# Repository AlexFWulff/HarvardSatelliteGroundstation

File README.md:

# Harvard Satellite Groundstation Code
This repository contains all the software for the groundstation, including OpenLST for the transmitter and Groundstation GNU Radio software.

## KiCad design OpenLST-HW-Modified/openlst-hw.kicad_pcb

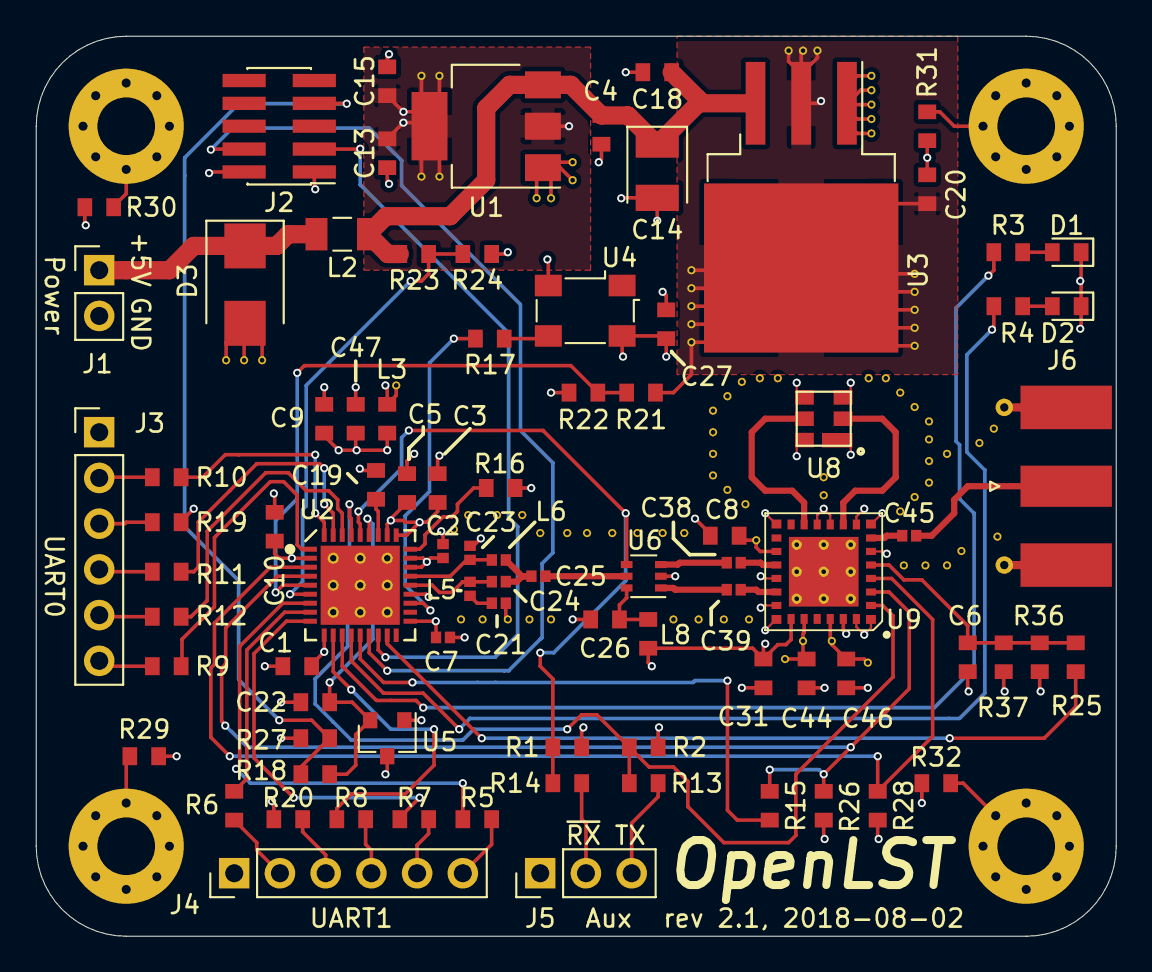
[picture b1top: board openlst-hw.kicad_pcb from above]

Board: 4 copper layers, 60.0 x 50.0 mm, 90 parts (0 on the bottom side), 65 nets.

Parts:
C1, C3, C5, C6, C8, C10, C15, C26, C27, C31: 0.1u; C_0603_1608Metric
C2, C7, C21, C25, C38, C39, C45: 220p; C_0402_1005Metric
C4, C13, C18, C20: 10u; C_0603_1608Metric
C9, C44, C46, C47: 1u; C_0603_1608Metric
C14: 100u; CP_EIA-3528-15_AVX-H
C19, C22: 1n; C_0603_1608Metric
C23, C24: 3.9p; C_0402_1005Metric
D1, D2: LED; LED_0603_1608Metric
D3: STPS340U; D_SMB
J1: 5VDC; PinHeader_1x02_P2.54mm_Vertical
J2: CC Prog/Debug; PinHeader_2x05_P1.27mm_Vertical_SMD
J3: UART0; PinHeader_1x06_P2.54mm_Vertical
J4: UART1; PinHeader_1x06_P2.54mm_Vertical
J5: Control Outputs; PinHeader_1x03_P2.54mm_Vertical
J6: ANT; SMA_Molex_73251-1153_EdgeMount_Horizontal
L2: Z=500 @ 100M; L_1206_3216Metric
L3, L8: Z=1k @ 100M; L_0603_1608Metric
L5, L6: 27n; L_0402_1005Metric
MK1, MK2, MK3, MK4: M3_Hole; MountingHole_3.2mm_M3_Pad_Via
R1, R2, R3, R4, R18, R26, R28: 1K; R_0603_1608Metric
R5, R6, R7, R8, R9, R10, R11, R12, R13, R14, R17: 100; R_0603_1608Metric
R15, R19, R20, R25, R29, R30, R31, R32: DNI; R_0603_1608Metric
R16: 56K; R_0603_1608Metric
R21, R23, R27: 33K; R_0603_1608Metric
R22, R24: 10K; R_0603_1608Metric
R36: 5K6; R_0603_1608Metric
R37: 3K3; R_0603_1608Metric
U1: LM1117-3.3; SOT-223-3_TabPin2
U2: CC1110; TI_CC_QFN36
U3: LT1086-3.6; TO-263-3_TabPin2
U4: FOX924 27MHz; Oscillator_SMD_Fordahl_DFAS15-4Pin_5.0x3.2mm
U5: TLV803S; SOT-23
U6: PE4259; SOT-363_SC-70-6
U8: STA1120A; SF2136E
U9: RFFM6403; Qorvo_LGA_28_ThermalVias

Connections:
+3V3: C13.1, C15.1, C27.1, C31.1, J2.2, L3.1, L8.1, R1.1, R19.1, R20.1, R26.1, R27.2, U1.2, U4.4, U5.3, U9.23
+5V: C4.1, C14.1, C18.1, L2.1, R23.2, U1.3, U3.3
/3V3_FILT: C1.1, C2.1, C3.1, C5.1, C7.1, C9.2, C10.1, C47.2, L3.2, U2.2, U2.10, U2.19, U2.22, U2.25, U2.26, U2.28, U2.29
/AN0: R21.1, R22.2, U2.5
/AN1: R23.1, R24.2, U2.6
/LST_TX_MODE: R2.2, R13.1, U2.33, U9.2
/PA_VAPC: C6.1, R25.1, R36.1, R37.2, U9.5
/PROG_DC: J2.3, U2.16
/PROG_DD: J2.4, U2.15
/RF_BYP: R28.1, U2.3, U9.4
/RF_EN: R15.1, R26.2, U2.4, U9.3
/UART0_CTS: J3.6, R9.2
/UART0_RTS: J3.2, R10.2
/UART0_RX: J3.4, R11.2
/UART0_TX: J3.5, R12.2
/UART1_CTS: J4.6, R5.2
/UART1_RTS: J4.2, R6.2
/UART1_RX: J4.4, R8.2
/UART1_TX: J4.5, R7.2
/~LST_RESET: J2.7, R18.2, R27.1
/~LST_RX_MODE: R1.2, R14.1, U2.32, U6.4
GND: C1.2, C2.2, C3.2, C4.2, C5.2, C6.2, C7.2, C8.2, C9.1, C10.2, C13.2, C14.2, C15.2, C18.2, C19.2, C20.2, C21.1, C22.2, C23.1, C26.2, C27.2, C31.2, C44.2, C46.2, C47.1, D1.1, D2.1, D3.2, J1.2, J2.1, J3.1, J4.1, J5.1, J6.2, R2.1, R16.1, R22.1, R24.1, R28.2, R29.1, R30.1, R31.1, R32.1, R36.2, U1.1, U2.37, U3.1, U4.2, U5.1, U6.2, U8.1, U8.3, U8.4, U8.5, U9.1, U9.6, U9.8, U9.9, U9.11, U9.12, U9.15, U9.19, U9.21, U9.22, U9.27, U9.28, U9.29
unnamed: C19.1, U2.30
unnamed: C21.2, L5.1
unnamed: C22.1, R18.1, U2.31, U5.2
unnamed: C23.2, L6.1, U2.24
unnamed: C24.1, L5.2, U2.23
unnamed: C24.2, C25.1, L6.2
unnamed: C25.2, U6.5
unnamed: C26.1, L8.2, U6.6
unnamed: C38.1, U6.3
unnamed: C38.2, U9.18
unnamed: C39.1, U6.1
unnamed: C39.2, U9.20
unnamed: C45.1, J6.1
unnamed: C45.2, U9.7
unnamed: D1.2, R3.1
unnamed: D2.2, R4.1
unnamed: D3.1, J1.1, L2.2
unnamed: J3.3, R19.2
unnamed: J4.3, R20.2
unnamed: J5.2, R14.2
unnamed: J5.3, R13.2
unnamed: MK1.1, R29.2
unnamed: MK2.1, R30.2
unnamed: MK3.1, R31.2
unnamed: MK4.1, R32.2
unnamed: R3.2, U2.12
unnamed: R4.2, U2.13
unnamed: R5.1, U2.7
unnamed: R6.1, U2.8
unnamed: R7.1, U2.9
unnamed: R8.1, U2.11
unnamed: R9.1, U2.1
unnamed: R10.1, U2.36
unnamed: R11.1, U2.35
unnamed: R12.1, U2.34
unnamed: R15.2, U2.14
unnamed: R16.2, U2.27
unnamed: R17.1, U4.3
unnamed: R17.2, U2.21
unnamed: R25.2, U2.17
unnamed: U8.2, U9.10
unnamed: U8.6, U9.13
VCC_3V6: C8.1, C20.1, C44.1, C46.1, R21.2, R37.1, U3.2, U9.17, U9.24, U9.26

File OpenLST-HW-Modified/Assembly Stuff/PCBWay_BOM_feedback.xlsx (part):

Reference | Value | Footprint | Datasheet | Manuf | ManufPN | Supplier | SupplierPN | Unit price | 5sets | PCBWay feedback | Customer Comments
L6 | 27n | Inductor_SMD:L_0402_1005Metric | http://search.murata.co.jp/Ceramy/image/img/P02/JELF243A-0050.pdf | Murata | LQW15AN27NJ00D | Digikey | 490-1151-1-ND | 0.105 | 0.52500000000000002
J6 | ANT | Connector_Coaxial:SMA_Molex_73251-1153_EdgeMount_Horizontal | https://www.molex.com/pdm_docs/sd/732511150_sd.pdf | Molex | 732511150 | Digikey | WM5534-ND | 4.83 | 24.15 | 5-7work days
C45 | 220p | Capacitor_SMD:C_0402_1005Metric | https://api.kemet.com/component-edge/download/datasheet/C040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 | Kemet | C0402C221J2GACAUTO | Digikey | 399-11552-1-ND | 0.315 | 1.575 | 5-7work days
C25 | 220p | Capacitor_SMD:C_0402_1005Metric | https://api.kemet.com/component-edge/download/datasheet/C040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 | Kemet | C0402C221J2GACAUTO | Digikey | 399-11552-1-ND | 0.315 | 1.575 | 5-7work days
C24 | 3.9p | Capacitor_SMD:C_0402_1005Metric | http://search.murata.co.jp/Ceramy/image/img/A01X/G101/ENG/GJ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 | Murata | GJM1555C1H3R9CB01D | Digikey | 490-3097-1-ND | 0.21 | 1.05 | 4300pcs
L5 | 27n | Inductor_SMD:L_0402_1005Metric | http://search.murata.co.jp/Ceramy/image/img/P02/JELF243A-0050.pdf | Murata | LQW15AN27NJ00D | Digikey | 490-1151-1-ND | 0.105 | 0.52500000000000002
C21 | 220p | Capacitor_SMD:C_0402_1005Metric | https://api.kemet.com/component-edge/download/datasheet/C040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 | Kemet | C0402C221J2GACAUTO | Digikey | 399-11552-1-ND | 0.315 | 1.575 | 5-7work days
U1 | LM1117-3.3 | Package_TO_SOT_SMD:SOT-223-3_TabPin2 | http://www.ti.com/lit/ds/symlink/lm1117.pdf | Texas Instruments | LM1117IMP-3.3/NOPB | Digikey | LM1117IMP-3.3/NOPBCT-ND | 0.73499999999999999 | 3.6749999999999998
C4 | 10u | Capacitor_SMD:C_0603_1608Metric | http://search.murata.co.jp/Ceramy/image/img/A01X/G101/ENG/GR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 | Murata | GRT188C81A106ME13D | Digikey | 490-12283-1-ND | 0.21 | 1.05
C13 | 10u | Capacitor_SMD:C_0603_1608Metric | http://search.murata.co.jp/Ceramy/image/img/A01X/G101/ENG/GR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 | Murata | GRT188C81A106ME13D | Digikey | 490-12283-1-ND | 0.21 | 1.05
C15 | 0.1u | Capacitor_SMD:C_0603_1608Metric | http://datasheets.avx.com/AutoMLCC.pdf | AVX | 0603YC104K4T4A | Digikey | 478-9382-1-ND | 0.105 | 0.52500000000000002
J1 | 5VDC | Connector_PinHeader_2.54mm:PinHeader_1x02_P2.54mm_Vertical |  |  |  |  |  | 0.105 | 0.52500000000000002 | 1*2pin header 2.54mm
D3 | STPS340U | Diode_SMD:D_SMB | http://www.st.com/content/ccc/resource/technical/document/da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 | STMicroelectronics | STPS340U | Digikey | 497-2465-1-ND | 0.315 | 1.575
L2 | Z=500 @ 100M | Inductor_SMD:L_1206_3216Metric | https://assets.lairdtech.com/home/brandworld/files/MI1206L50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 | Laird | MI1206L501R-10 | Digikey | 240-2407-1-ND | 0.63 | 3.15 | 5-7work days
C14 | 100u | Capacitor_Tantalum_SMD:CP_EIA-3528-15_AVX-H | http://datasheets.avx.com/TPS.pdf | AVX | TPSB107M010R0400 | Digikey | 478-5231-1-ND | 0.63 | 3.15 | 470pcs
U3 | LT1086-3.6 | Package_TO_SOT_SMD:TO-263-3_TabPin2 | http://www.linear.com/docs/1722 | Linear | LT1086CM-3.6#PBF | Digikey | LT1086CM-3.6#PBF-ND | 7.2450000000000001 | 36.225000000000001 | 5-7work days
C46 | 1u | Capacitor_SMD:C_0603_1608Metric | http://www.samsungsem.com/kr/support/product-search/mlcc/CL1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 | Samsung | CL10B105MO8NNWC | Digikey | 1276-6524-6-ND | 0.105 | 0.52500000000000002
C44 | 1u | Capacitor_SMD:C_0603_1608Metric | http://www.samsungsem.com/kr/support/product-search/mlcc/CL1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 | Samsung | CL10B105MO8NNWC | Digikey | 1276-6524-6-ND | 0.105 | 0.52500000000000002
U6 | PE42359 |  |  | pSemi | PE42359SCAA-Z | Digikey | 1046-1077-1-ND |  |  | Out of stock, any replaced parts? | Replaced with in-stock part!
C38 | 220p | Capacitor_SMD:C_0402_1005Metric | https://api.kemet.com/component-edge/download/datasheet/C040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 | Kemet | C0402C221J2GACAUTO | Digikey | 399-11552-1-ND | 0.315 | 1.575 | 5-7work days
C39 | 220p | Capacitor_SMD:C_0402_1005Metric | https://api.kemet.com/component-edge/download/datasheet/C040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 | Kemet | C0402C221J2GACAUTO | Digikey | 399-11552-1-ND | 0.315 | 1.575 | 5-7work days
C26 | 0.1u | Capacitor_SMD:C_0603_1608Metric | http://datasheets.avx.com/AutoMLCC.pdf | AVX | 0603YC104K4T4A | Digikey | 478-9382-1-ND | 0.105 | 0.52500000000000002
U2 | CC1110 | openlst:TI_CC_QFN36 | http://www.ti.com/lit/ds/symlink/cc1110-cc1111.pdf | Texas Instruments | CC1110F32RHHR | Digikey | 296-38560-1-ND | 8.19 | 40.949999999999996 | 5-7work days
U5 | TLV803S | Package_TO_SOT_SMD:SOT-23 | http://www.ti.com/lit/ds/symlink/tlv803.pdf | Texas Instruments | TLV803SDBZR | Digikey | 296-29196-1-ND | 0.315 | 1.575
R18 | 1K | Resistor_SMD:R_0603_1608Metric | http://www.yageo.com/documents/recent/PYu-RC_Group_51_RoHS_L_9.pdf | Yageo | RC0603JR-071KL | Digikey | 311-1.0KGRCT-ND | 5.2499999999999998E-2 | 0.26250000000000001
C22 | 1n | Capacitor_SMD:C_0603_1608Metric | https://www.murata.com/~/media/webrenewal/support/library/ca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 | Murata | GCM188R71E102KA37D | Digikey | 490-8016-1-ND | 5.2499999999999998E-2 | 0.26250000000000001
R16 | 56K | Resistor_SMD:R_0603_1608Metric | https://www.seielect.com/Catalog/SEI-RMCF_RMCP.pdf | Stackpole | RMCF0603FT56K0 | Digikey | RMCF0603FT56K0CT-ND | 5.2499999999999998E-2 | 0.26250000000000001
C19 | 1n | Capacitor_SMD:C_0603_1608Metric | https://www.murata.com/~/media/webrenewal/support/library/ca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 | Murata | GCM188R71E102KA37D | Digikey | 490-8016-1-ND | 5.2499999999999998E-2 | 0.26250000000000001
J2 | CC Prog/Debug | Connector_PinHeader_1.27mm:PinHeader_2x05_P1.27mm_Vertical_SMD | http://suddendocs.samtec.com/prints/ftsh-1xx-xx-xxx-dv-xxx-x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 | Samtec | FTSH-105-01-L-DV-K-P | Digikey | SAM9076-ND | 5.04 | 25.2 | 5-7work days
R5 | 100 | Resistor_SMD:R_0603_1608Metric | http://www.yageo.com/NewPortal/yageodocoutput?fileName=/pdf/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 | Yageo | AC0603FR-07100RL | Digikey | YAG3561CT-ND | 5.2499999999999998E-2 | 0.26250000000000001
R6 | 100 | Resistor_SMD:R_0603_1608Metric | http://www.yageo.com/NewPortal/yageodocoutput?fileName=/pdf/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 | Yageo | AC0603FR-07100RL | Digikey | YAG3561CT-ND | 5.2499999999999998E-2 | 0.26250000000000001
R7 | 100 | Resistor_SMD:R_0603_1608Metric | http://www.yageo.com/NewPortal/yageodocoutput?fileName=/pdf/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 | Yageo | AC0603FR-07100RL | Digikey | YAG3561CT-ND | 5.2499999999999998E-2 | 0.26250000000000001
R8 | 100 | Resistor_SMD:R_0603_1608Metric | http://www.yageo.com/NewPortal/yageodocoutput?fileName=/pdf/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 | Yageo | AC0603FR-07100RL | Digikey | YAG3561CT-ND | 5.2499999999999998E-2 | 0.26250000000000001
R9 | 100 | Resistor_SMD:R_0603_1608Metric | http://www.yageo.com/NewPortal/yageodocoutput?fileName=/pdf/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 | Yageo | AC0603FR-07100RL | Digikey | YAG3561CT-ND | 5.2499999999999998E-2 | 0.26250000000000001
R10 | 100 | Resistor_SMD:R_0603_1608Metric | http://www.yageo.com/NewPortal/yageodocoutput?fileName=/pdf/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 | Yageo | AC0603FR-07100RL | Digikey | YAG3561CT-ND | 5.2499999999999998E-2 | 0.26250000000000001
R11 | 100 | Resistor_SMD:R_0603_1608Metric | http://www.yageo.com/NewPortal/yageodocoutput?fileName=/pdf/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 | Yageo | AC0603FR-07100RL | Digikey | YAG3561CT-ND | 5.2499999999999998E-2 | 0.26250000000000001
R12 | 100 | Resistor_SMD:R_0603_1608Metric | http://www.yageo.com/NewPortal/yageodocoutput?fileName=/pdf/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 | Yageo | AC0603FR-07100RL | Digikey | YAG3561CT-ND | 5.2499999999999998E-2 | 0.26250000000000001
C31 | 0.1u | Capacitor_SMD:C_0603_1608Metric | http://datasheets.avx.com/AutoMLCC.pdf | AVX | 0603YC104K4T4A | Digikey | 478-9382-1-ND | 0.105 | 0.52500000000000002
R28 | 1K | Resistor_SMD:R_0603_1608Metric | http://www.yageo.com/documents/recent/PYu-RC_Group_51_RoHS_L_9.pdf | Yageo | RC0603JR-071KL | Digikey | 311-1.0KGRCT-ND | 5.2499999999999998E-2 | 0.26250000000000001
R26 | 1K | Resistor_SMD:R_0603_1608Metric | http://www.yageo.com/documents/recent/PYu-RC_Group_51_RoHS_L_9.pdf | Yageo | RC0603JR-071KL | Digikey | 311-1.0KGRCT-ND | 5.2499999999999998E-2 | 0.26250000000000001
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
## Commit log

2019-03-02 Added OpenLST files
2019-03-02 Added ReadMe
2019-04-02 Added hardware files
2019-09-17 Duplicated hardware project files before Kicad edits
2019-09-18 Changed Kicad file with updated SAW filter
2019-09-20 Changed kicad before manufacturing
2019-09-20 Re-added OpenLST-HW-Modified directory to remove submodule
2019-10-05 Added test radio target under OpenLST/radios
2019-11-02 Subtle modifications
2019-11-02 Kit_UART skeleton
2019-11-04 Made changes to makefile to be able to make test_radio
2019-11-05 Initial changes to support custom messages

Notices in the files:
OpenLST-HW-Modified/openlst-hw.kicad_pcb:
This work is licensed under a
Creative Commons Attribution-ShareAlike 4.0
International License (CC-BY-SA 4.0).
